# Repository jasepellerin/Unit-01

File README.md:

# Unit-01 Firmware & Keymap

## What is this?

Unit-01 is the first keyboard I've designed and my first real foray into electronics as a whole. Unit-01 is a split, ergonomic, columnar, bluetooth, 32-key keyboard designed to be built using [nice!nano](https://nicekeyboards.com/nice-nano/) boards and Kailh Choc switches.

## Repo info

- Top level - ZMK config and related files
- "ergogen" - files related to the tool used to design the PCB and basic case elements
- "case" - case models and related files

## ZMK Process

### Shield creation / basic setup

Started by creating `boards/shields` files manually based on the [card](https://github.com/benvallack/zmk-config-card/tree/master/config/boards/shields/card) and the [a_dux](https://github.com/zmkfirmware/zmk/tree/main/app/boards/shields/a_dux)

### Initial key mapping

Moved into using [keymapper](https://www.keymapper.dev/layout) to generate base key layout with layers

- Start with 12 columns and 4 rows
- Delete the keys we don't need (double click)
- Scooch the right side over a bit (15 or so)
- Backup often :D

### Complex key mapping

Moved back into the raw keymap file for more precise control over the keys

## How to run the formatter

1. Commit or save your current work in case things get wild
1. Add line breaks between your rows to define the basic shape of your board
1. Steal the `format.ts` file and put it wherever you like
1. Install a typescript runner like [esrun](https://www.npmjs.com/package/@digitak/esrun) with `npm i -g @digitak/esrun`
1. Add your `filePath` and `desiredKeyCharacters` variables in `format.ts`
1. Run with esrun format.ts
1. Tweak the output to match your formatting needs
1. Run again after you change stuff :D

---

## Project log

### Initial Idea

I had been curious about split ergonomic keyboards for a few years when I saw a few of Ben Vallack's videos on small custom keyboards. [This one in particular](https://www.youtube.com/watch?v=UKfeJrRIcxw) sparked my interest in designing and building my own board. I asked loads of questions on various Discord servers along the way, and sincerely appreciate all the help I received from the community.

### Ideation

I did some research to learn about different switch options and elements I might want on my board. I started looking other people's builds, like the [Architeuthis dux](https://github.com/tapioki/cephalopoda/tree/main/Architeuthis%20dux) and the [card](https://github.com/benvallack/ergogen/blob/master/config.yaml). This helped me decide on the basic shape of the board and how many keys it would have.

### PCB Design (Ergogen)

I began by measuring the natural paths of my fingers on a site called [Ergopad](https://pashutk.ru/ergopad/). Then I plugged that info into [the unofficial Ergogen frontend](https://ergogen.cache.works/) and spent probably 25 hours learning the syntax and tweaking positions.

Then I started tweaking the exported file in Kicad. While adding my traces, I kept learning new things which led me back into Ergogen for another iteration cycle. Overall, this process probably took 15 more hours.

### Part Ordering

At this time, I had all the necessary files to start ordering parts. Here's the total cost of parts I ordered (a detailed breakdown is available by expanding the section below):

**Total part costs**

| Item        |   Price |
| :---------- | ------: |
| Subtotal    | $134.81 |
| S/H         |  $19.48 |
| Grand Total | $154.29 |

<details>
  <summary>Detailed cost breakdown</summary>

[Boardsource](https://boardsource.xyz/)

| Item                           | Price |
| :----------------------------- | ----: |
| 40x Kailh Choc hotswap sockets |    $6 |
| S/H                            |    $4 |
| Order total                    |   $10 |

[MKULTRA](https://mkultra.click/)

| Item                             |  Price |
| :------------------------------- | -----: |
| 40x Kailh Choc Switches (Silver) | $28.60 |
| White MBK Choc Keycaps (Alphas)  |    $15 |
| S/H                              |  $5.59 |
| Order total                      | $49.19 |

[Little Keyboards](https://www.littlekeyboards.com/)

| Item                                      |  Price |
| :---------------------------------------- | -----: |
| 2x nice!nano v2.0                         | $49.98 |
| 2x Battery Combo for nice!nano Controller | $23.98 |
| S/H                                       |  $4.83 |
| Total                                     | $78.79 |

[JLCPCB](https://jlcpcb.com/)

| Item          |  Price |
| :------------ | -----: |
| 5x Custom PCB |  $9.25 |
| S/H           |  $4.06 |
| Total         | $13.31 |

[LCSC](https://lcsc.com/) - Part of a larger order

| Item    | Price |
| :------ | ----: |
| Buttons |   ~$2 |
| S/H     |    ~1 |
| Total   |    $3 |

</details>

### Assembly

After I received all the parts, I spent ~4 hours soldering everything. This step took a while since this was the first time I've ever soldered anything. Overall, it was pretty straightforward and I could feel myself getting more comfortable as I went.

I then spent around 8 hours debugging and fixing mistakes before I finally had a working keyboard.

### Firmware (ZMK)

The next step was setting up the firmware using [ZMK](https://zmk.dev/docs/), which probably took around 4 hours to learn and customize. I expect spend even more time on this stage getting all the keys laid out just how I want them.

### Case Design (Fusion 360)

Once everything was working to my liking, I decided to design a case for the keyboard. I spent probably 5 hours designing the case and another 1-2 hours messing with the 3D printer and fitting everything together.

### Conclusion

Overall, this build took me around 60 hours to complete. I started out not knowing anything about keyboard building or PCB design, I didn't even know how to solder!

I'm extremely pleased with how the board has turned out and am excited to actually use it now that it's done :D

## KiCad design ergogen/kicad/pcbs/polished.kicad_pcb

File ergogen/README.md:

# Ergogen

Ergogen is a keyboard generator that aims to provide a common configuration format to describe **ergonomic** 2D layouts, and generate automatic plates, cases, and (un-routed) PCBs for them.
The project grew out of (and is an integral part of) the [Absolem keyboard](https://zealot.hu/absolem), and shares its [Discord server](https://discord.gg/nbKcAZB) as well.

For usage and config information, please refer to the [docs](https://docs.ergogen.xyz).

## How to use

The main file to mess with is "config.yaml", which describes how the keyboard should be constructed using Ergogen's syntax. Pasting that file's contents into [this site](https://ergogen.cache.works/) will build the 2D and 3D representations of the keyboard and basic case structure.

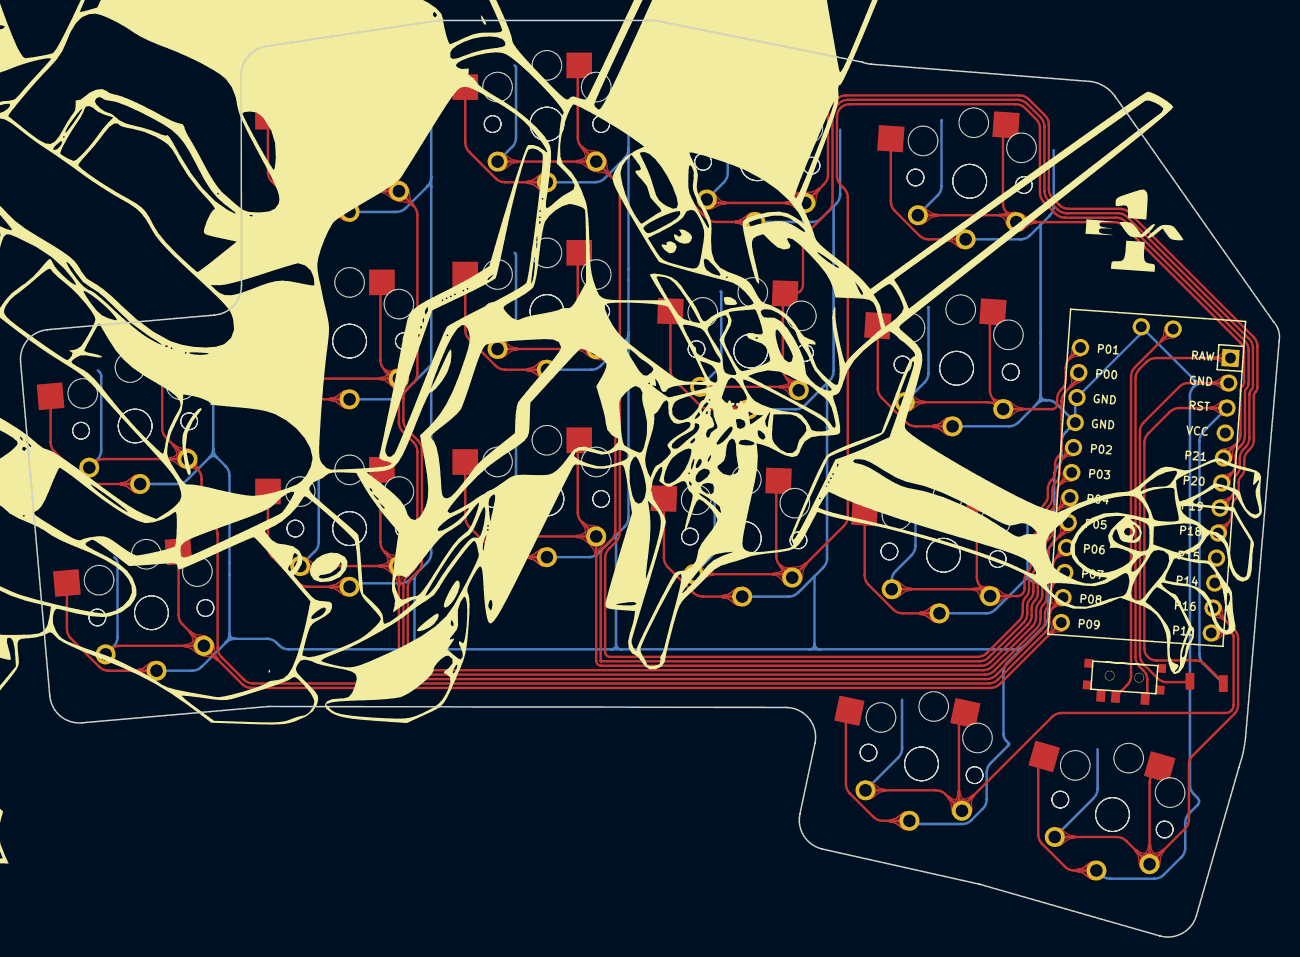
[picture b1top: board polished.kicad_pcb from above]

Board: 2 copper layers, 127.6 x 92.9 mm, 34 parts (0 on the bottom side), 18 nets.

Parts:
MCU1: ProMicro
S1, S2, S3, S4, S5, S6, S7, S8, S9, S10, S11, S12, S13, S14, S15, S16, S17, S18, S19, S20, S21, S22, S23, S24, S25, S26, S27, S28, S29, S30, S31, S32: PG1350
T1: SPDT_C128955

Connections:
GND: MCU1.2, MCU1.15, MCU1.16, S1.2, S2.2, S3.2, S4.2, S5.2, S6.2, S7.2, S8.2, S9.2, S10.2, S11.2, S12.2, S13.2, S14.2, S15.2, S16.2, S17.2, S18.2, S19.2, S20.2, S21.2, S22.2, S23.2, S24.2, S25.2, S26.2, S27.2, S28.2, S29.2, S30.2, S31.2, S32.2
P0: MCU1.14, S23.1, S24.1
P1: MCU1.13, S25.1, S26.1
P2: MCU1.17, S15.1, S16.1
P3: MCU1.18, S13.1, S14.1
P4: MCU1.19, S11.1, S12.1
P5: MCU1.20, S9.1, S10.1
P6: MCU1.21, S7.1, S8.1
P7: MCU1.22, S5.1, S6.1
P8: MCU1.23, S3.1, S4.1
P9: MCU1.24, S1.1, S2.1
P10: MCU1.12, S29.1, S30.1
P16: MCU1.11, S31.1, S32.1
P18: MCU1.8, S21.1, S22.1
P19: MCU1.7, S19.1, S20.1
P20: MCU1.6, S17.1, S18.1
P21: MCU1.5, S27.1, S28.1
RAW: MCU1.1, T1.1

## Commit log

2022-03-12 Cleanup
2022-03-12 Starting outlines
2022-03-12 Standardize some units
2022-03-12 Clean up variables
2022-03-12 Remove lots of cruft, tighten up the outline
2022-03-12 Lots of cleanup and tweaking
2022-03-12 Cleanup, added visual units
2022-03-12 Adding fillet, moving mcu
2022-03-12 More moving pieces, quite pleased with the outline now
2022-03-12 Flip mcu
2022-03-12 Small thumbpad tweak, start wiring
2022-03-12 More wiring, tweak bottom of outline
2022-03-12 Add wiring space at the bottom, re-add choc hotswap (whoops!)
2022-03-13 Move index columns in
2022-03-13 Bring in thumb fan
2022-03-13 Use config.yaml
2022-03-13 Remove unused stuff
2022-03-13 Add footprints
2022-03-13 Symlink and ignore config
2022-03-13 Export new footprints
2022-03-13 Remove battery footprint
2022-03-14 Add power switch and reset button
2022-03-14 Re-add button and switch
2022-03-14 Fix button nets
2022-03-14 Tweak button, add button connector, then comment out switch and connector for the first round
2022-03-14 Re-add switch, add batteryPads, move switch over a bit
2022-03-14 Add battery pads, remove switch
2022-03-14 Swapping some pins while wiring things up in kicad
2022-03-14 Add kicad files
2022-03-15 Generate pcb
2022-03-17 Make outline match tweaks I made in Kicad
2022-03-17 Add basic case
2022-03-17 Add adjusted kicad, based on tweaks to ergogen
2022-04-03 Initial User Config.
2022-04-04 First attempt at custom shield
2022-04-04 Fix west and keymap
2022-04-04 Fix build.yaml
2022-04-04 Fix overlays
2022-04-04 Try simplifying keymap
2022-04-04 Replace tabs
2022-04-04 Cleanup and moving things around
2022-04-04 Fix defconfig
2022-04-04 Fix defconfig naming
2022-04-04 Rename to fit in BT limit
2022-04-04 Temp bluetooth clear
2022-04-04 Add bt
2022-04-04 All bt clear
2022-04-04 Add bootloader button, fix number of columns
2022-04-04 Fix spacing
2022-04-04 Add settings reset
2022-04-04 Update copyright
2022-04-04 Re-add normal keys
2022-04-04 Try col-gpios
2022-04-04 Disable sleep
2022-04-04 Back to input
2022-04-04 Try bt clr again
2022-04-04 Try adux firmware
2022-04-04 Try nice_nano without v2
2022-04-04 All bt clear again
2022-04-04 Trying with built boards
2022-04-04 Trying with built boards - fixed
2022-04-04 Trying with built boards - again
2022-04-04 Remove comments
2022-04-04 Remove whitespace
2022-04-04 Fix kp
2022-04-05 All bootloader
2022-04-05 Logging
2022-04-05 One key
2022-04-05 BT Clear on thumbs
2022-04-05 Trying with a stock shield
2022-04-05 Trying with a stock shield for real tho
2022-04-05 Trying with a stock shield for real tho x2
2022-04-05 Remove logging
2022-04-05 Shrug
2022-04-05 Back to normal builds
2022-04-05 Case stuff
2022-04-05 Unignore config
2022-04-05 Add test shield
2022-04-05 Add overlay
2022-04-06 Use keymap editor to make some layers and whatnot
2022-04-06 Fix undefined
2022-04-07 Add quick release to sk
2022-04-07 Remove logging, increase BT power
2022-04-07 Remove shield conf files
2022-04-07 Update keymap
2022-04-07 Fix other undefined
2022-04-07 Fix null play pause btn
2022-04-07 Readme updates
2022-04-07 Moved backspace and return
2022-04-07 Simple formatting
2022-04-07 Add auto-formatter and format
2022-04-07 Documentation
2022-04-07 Documentation warning :p
2022-04-07 Fix formatting error
2022-04-07 Fix formatter, add more spacing to my layout
2022-04-07 Use smaller definitions, clean up some codes
2022-04-07 Swap backspace and return
2022-04-07 Comma and dot
2022-04-07 Tabbing, homerow mods, MEH
2022-04-07 Fix formatting issue
2022-04-07 Put behaviors in the maybe right place
2022-04-07 Try simple tapdance
2022-04-07 Try different naming
2022-04-07 Different-er naming
2022-04-07 Actually read the docs
2022-04-07 BT clearing and nav
2022-04-07 Sleep
2022-04-07 Fix typo
2022-04-07 Fix homerow mods
2022-04-07 Fix transparency
2022-04-10 Add ergogen repo into its own directory
2022-04-10 Add case files and render image
2022-04-10 Crop image and fix readme link
2022-04-10 Remove todo in favor of issues
2022-04-10 Remove ergogen todos, add how to
2022-04-10 Naming
2022-04-10 Remove old kicad files, rename
2022-04-10 Remove old kicad files, rename, move image to top level folder
2022-04-10 Pricing table
2022-04-10 Doc structuring
2022-04-10 Hide cost breakdown
2022-04-10 Details
2022-04-11 Added more depth to main case body
2022-04-13 Updated case
2022-04-26 Trying a couple things
2022-04-26 Alt tab
2022-04-27 Formatting, rh bt clear
2022-04-27 Trying a new layer, a bit lost in the weeds
2022-04-27 Fix schema
2022-04-27 Fix combo
2022-04-27 Add semi
2022-04-27 Replace LM with LG
2022-04-27 Try working keymap to test firmware gen
2022-04-27 Revert, add reset bindings
2022-04-27 Fix naming issues
2022-04-27 Add base from movement
2022-04-27 Fix combos
2022-04-27 Move some things
2022-04-27 Move chrome tab keys over one
2022-04-29 Add more images
2022-09-27 Add quick tabbing, layer tap to movement
2022-09-27 Remove shift from super thumb key
2022-09-27 Make SYMBOLS sticky
2022-09-27 Movement layer alt tab
2022-09-27 Fix left alt
2022-09-28 Simplify, adding tab to movement layer
2022-09-28 Update symbols layer heavily, add F keys and more movement
2022-09-28 Lots of random improvements
2022-09-28 Fix missing /
2022-09-28 Fix binding
2022-09-28 Fix qt
2022-09-28 Test without new stuff
2022-09-28 GQT to HM
2022-09-28 Swap lingering GQT
2022-09-28 Add moto second param
2022-09-28 Swap tilde, add pipe
2022-09-28 Longer homerow tap term
2023-04-03 Trying out qwerty
2023-06-09 Improvements
2023-06-09 Update reset name
2023-06-09 Use keymap upgrader
